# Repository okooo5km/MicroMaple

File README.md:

# Micro Maple

**Micro Maple** is an opensource hardware like **Maple mini** created by Leaflab and disigned to realize our idea and creat our works more quickly and simply ! 

Basically, **STM32F103C8T6** works as the core -- it's very cheap and enough for our most ideas!

The features of **STM32F103C8T6**:

- ARM 32bits Cortex-M3 CPU
  - 72MHz, 1.25DMips/MHz(Dhrystone 2.1)
  - single cycle for Multiplication and Division
- 64K FLASH And 20K SRAM
- Two 12bits ADC, 1 us for transition
- 7 channel DMA for USART\Timer\ADC\SPI\IIC
- 16 External Interrupt
- 7 Timer
- Interface
  - 2 IIC
  - 3 USART
  - 3 SPI
  - CAN
  - USB2.0

# Micro Maple (中文)

**Micro Maple** 是类似于 **Maple Mini(由Leaflab设计)** 的开源硬件，设计初衷是让我们实现自己的想法和作品更加简单和快捷。

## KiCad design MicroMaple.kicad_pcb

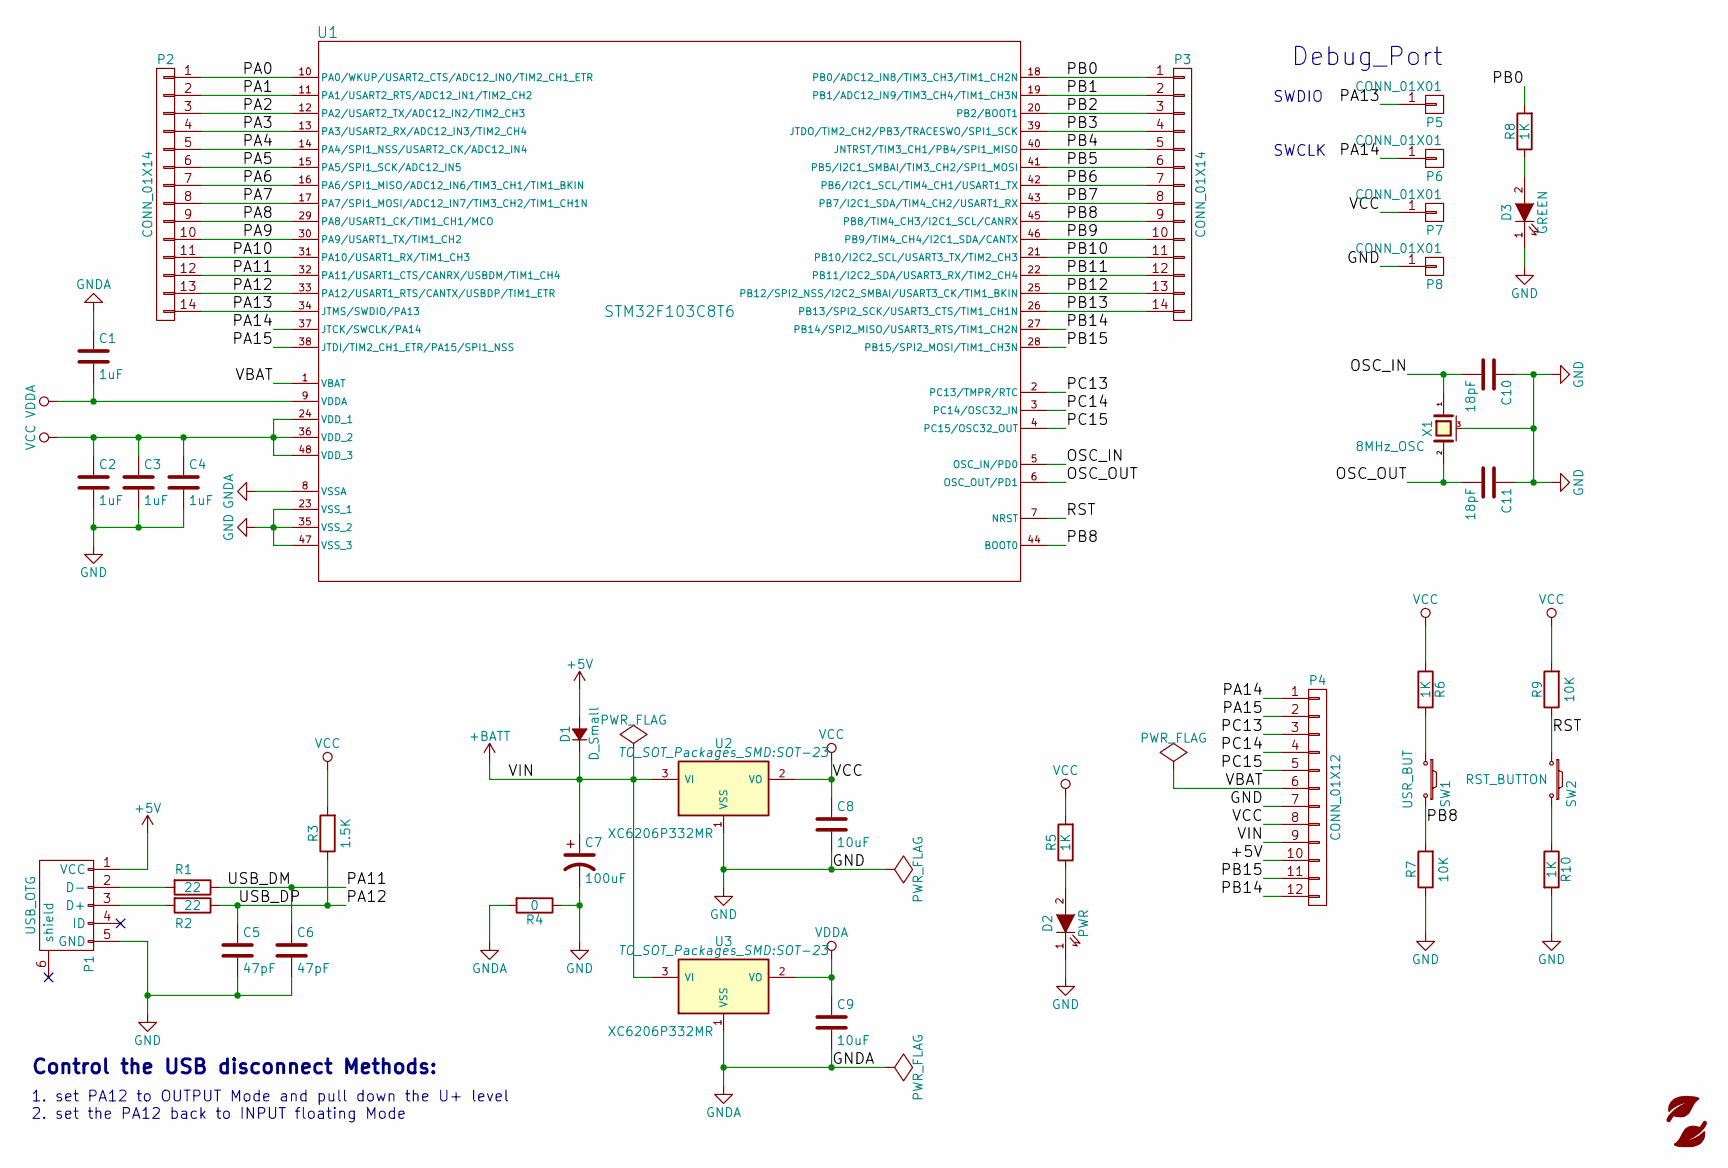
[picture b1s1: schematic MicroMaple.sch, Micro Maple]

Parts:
C1, C2, C3, C4: 1uF; C_0603
C5, C6: 47pF; C_0603
C7: 100uF; SMD-1210_Pol
C8, C9: 10uF; C_0603
C10, C11: 18pF; C_0603
D1: D_Small; SOD-123
D2: PWR; LED_0603
D3: GREEN; LED_0603
P1: USB_OTG; USB_Micro-B-MK5
P2, P3: CONN_01X14; Connector_FAD_14x1
P4: CONN_01X12; Connector_FAD_12x1
P5, P6, P7, P8: CONN_01X01; Debug_Pin_1
R1, R2: 22; R_0603
R3: 1.5K; R_0603
R4: 0; R_0603
R5, R6, R8, R10: 1K; R_0603
R7, R9: 10K; R_0603
SW1: USR_BUT; SW_SPST_EVQP7C
SW2: RST_BUTTON; SW_SPST_EVQP7C
U1: STM32F103C8T6; LQFP-48_7x7mm_Pitch0.5mm
U2, U3: XC6206P332MR; SOT-23
X1: 8MHz_OSC; Resonator_3.2x1.5mm

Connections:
+5V: D1.2 (A), P1.1 (VCC), P4.10
+BATT: C7.1, D1.1 (K), P4.9, U2.3 (VI), U3.3 (VI)
/OSC_IN: C10.2, U1.5 (OSC_IN/PD0), X1.1
/OSC_OUT: C11.2, U1.6 (OSC_OUT/PD1), X1.2
/PA0: P2.1, U1.10 (PA0/WKUP/USART2_CTS/ADC12_IN0/TIM2_CH1_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)
/PA1: P2.2, U1.11 (PA1/USART2_RTS/ADC12_IN1/TIM2_CH2)
/PA2: P2.3, U1.12 (PA2/USART2_TX/ADC12_IN2/TIM2_CH3)
/PA3: P2.4, U1.13 (PA3/USART2_RX/ADC12_IN3/TIM2_CH4)
/PA4: P2.5, U1.14 (PA4/SPI1_NSS/USART2_CK/ADC12_IN4)
/PA5: P2.6, U1.15 (PA5/SPI1_SCK/ADC12_IN5)
/PA6: P2.7, U1.16 (PA6/SPI1_MISO/ADC12_IN6/TIM3_CH1/TIM1_B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)
/PA7: P2.8, U1.17 (PA7/SPI1_MOSI/ADC12_IN7/TIM3_CH2/TIM1_C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)
/PA8: P2.9, U1.29 (PA8/USART1_CK/TIM1_CH1/MCO)
/PA9: P2.10, U1.30 (PA9/USART1_TX/TIM1_CH2)
/PA10: P2.11, U1.31 (PA10/USART1_RX/TIM1_CH3)
/PA11: C6.1, P2.12, R1.1, U1.32 (PA11/USART1_CTS/CANRX/USBDM/TIM1_CH4)
/PA12: C5.1, P2.13, R2.1, R3.1, U1.33 (PA12/USART1_RTS/CANTX/USBDP/TIM1_ETR)
/PA13: P2.14, P5.1, U1.34 (JTMS/SWDIO/PA13)
/PA14: P4.1, P6.1, U1.37 (JTCK/SWCLK/PA14)
/PA15: P4.2, U1.38 (JTDI/TIM2_CH1_ETR/PA15/SPI1_NSS)
/PB0: P3.1, R8.2, U1.18 (PB0/ADC12_IN8/TIM3_CH3/TIM1_CH2N)
/PB1: P3.2, U1.19 (PB1/ADC12_IN9/TIM3_CH4/TIM1_CH3N)
/PB2: P3.3, U1.20 (PB2/BOOT1)
/PB3: P3.4, U1.39 (JTDO/TIM2_CH2/PB3/TRACESWO/SPI1_SCK)
/PB4: P3.5, U1.40 (JNTRST/TIM3_CH1/PB4/SPI1_MISO)
/PB5: P3.6, U1.41 (PB5/I2C1_SMBAI/TIM3_CH2/SPI1_MOSI)
/PB6: P3.7, U1.42 (PB6/I2C1_SCL/TIM4_CH1/USART1_TX)
/PB7: P3.8, U1.43 (PB7/I2C1_SDA/TIM4_CH2/USART1_RX)
/PB8: P3.9, R7.2, SW1.2, U1.44 (BOOT0), U1.45 (PB8/TIM4_CH3/I2C1_SCL/CANRX)
/PB9: P3.10, U1.46 (PB9/TIM4_CH4/I2C1_SDA/CANTX)
/PB10: P3.11, U1.21 (PB10/I2C2_SCL/USART3_TX/TIM2_CH3)
/PB11: P3.12, U1.22 (PB11/I2C2_SDA/USART3_RX/TIM2_CH4)
/PB12: P3.13, U1.25 (PB12/SPI2_NSS/I2C2_SMBAI/USART3_CK/TIM1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)
/PB13: P3.14, U1.26 (PB13/SPI2_SCK/USART3_CTS/TIM1_CH1N)
/PB14: P4.12, U1.27 (PB14/SPI2_MISO/USART3_RTS/TIM1_CH2N)
/PB15: P4.11, U1.28 (PB15/SPI2_MOSI/TIM1_CH3N)
/PC13: P4.3, U1.2 (PC13/TMPR/RTC)
/PC14: P4.4, U1.3 (PC14/OSC32_IN)
/PC15: P4.5, U1.4 (PC15/OSC32_OUT)
/RST: R9.1, SW2.1, U1.7 (NRST)
/VBAT: P4.6, U1.1 (VBAT)
GND: C2.2, C3.2, C4.2, C5.2, C6.2, C7.2, C8.2, C10.1, C11.1, D2.1 (K), D3.1 (K), P1.5 (GND), P4.7, P8.1, R4.1, R7.1, R10.2, U1.23 (VSS_1), U1.35 (VSS_2), U1.47 (VSS_3), U2.1 (VSS), X1.3 (case)
GNDA: C1.1, C9.2, R4.2, U1.8 (VSSA), U3.1 (VSS)
unnamed: D2.2 (A), R5.1
unnamed: D3.2 (A), R8.1
unnamed: P1.2 (D-), R1.2
unnamed: P1.3 (D+), R2.2
unnamed: R6.2, SW1.1
unnamed: R10.1, SW2.2
VCC: C2.1, C3.1, C4.1, C8.1, P4.8, P7.1, R3.2, R5.2, R6.1, R9.2, U1.24 (VDD_1), U1.36 (VDD_2), U1.48 (VDD_3), U2.2 (VO)
VDDA: C1.2, C9.1, U1.9 (VDDA), U3.2 (VO)

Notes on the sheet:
Debug_Port
SWDIO
SWCLK
Control the USB disconnect Methods:
1. set PA12 to OUTPUT Mode and pull down the U+ level 2. set the PA12 back to INPUT floating Mode

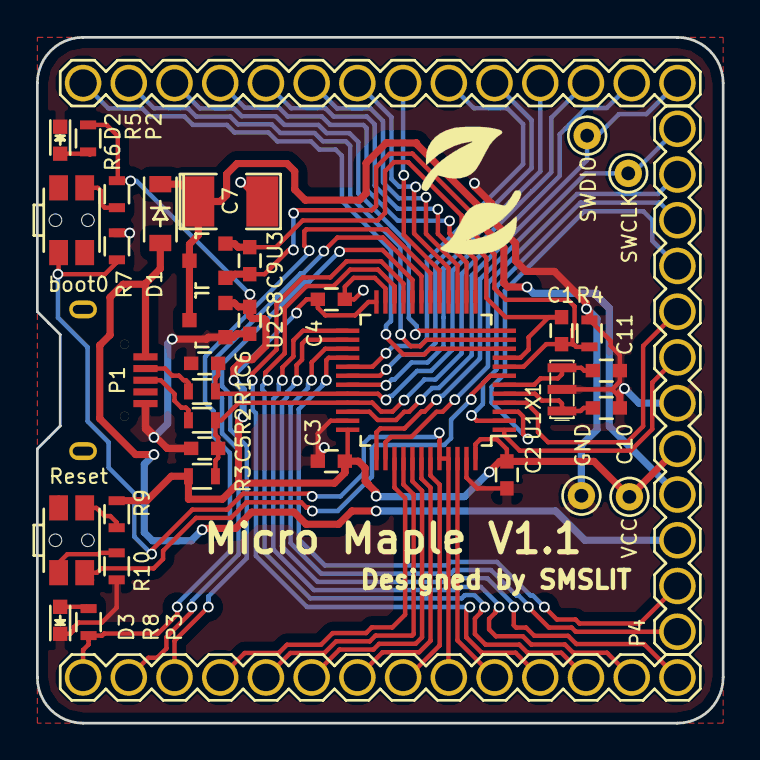
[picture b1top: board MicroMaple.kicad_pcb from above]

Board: 2 copper layers, 38.1 x 38.1 mm, 38 parts (0 on the bottom side), 51 nets.

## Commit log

2016-10-08 add the some libs
2016-10-08 add the readme doc
2016-10-08 finish the sch, and assign some footprints, update the README.md
2016-10-09 finish assign the footprints and begin the PCB design
2016-10-09 finish the PCB layout and track
2016-10-10 finish the PCB design
2016-10-10 optimize the layout and tracks, then add the logo and some text
2016-10-10 plot the gerber files and drill file
2016-10-11 export the BOM
2016-10-12 update the sch file
2016-10-17 update the sch-pdf
2016-10-18 1.remove the USB disconnect circuit. 2.export v1.1 pdf. 3.add smslit logo lib
2016-10-19 add the pinmap xlsx file and encorrect the Bsilks text for pins.
2016-10-23 Micro Maple Version1.1 : 1. update the sch and netlist file; 2. finish pcb trace layout
2016-10-24 V1.1: update the pcb desgin
2016-10-30 because the mistake in m2OLED pcb design, change the position of GND\VCC\VBAT
